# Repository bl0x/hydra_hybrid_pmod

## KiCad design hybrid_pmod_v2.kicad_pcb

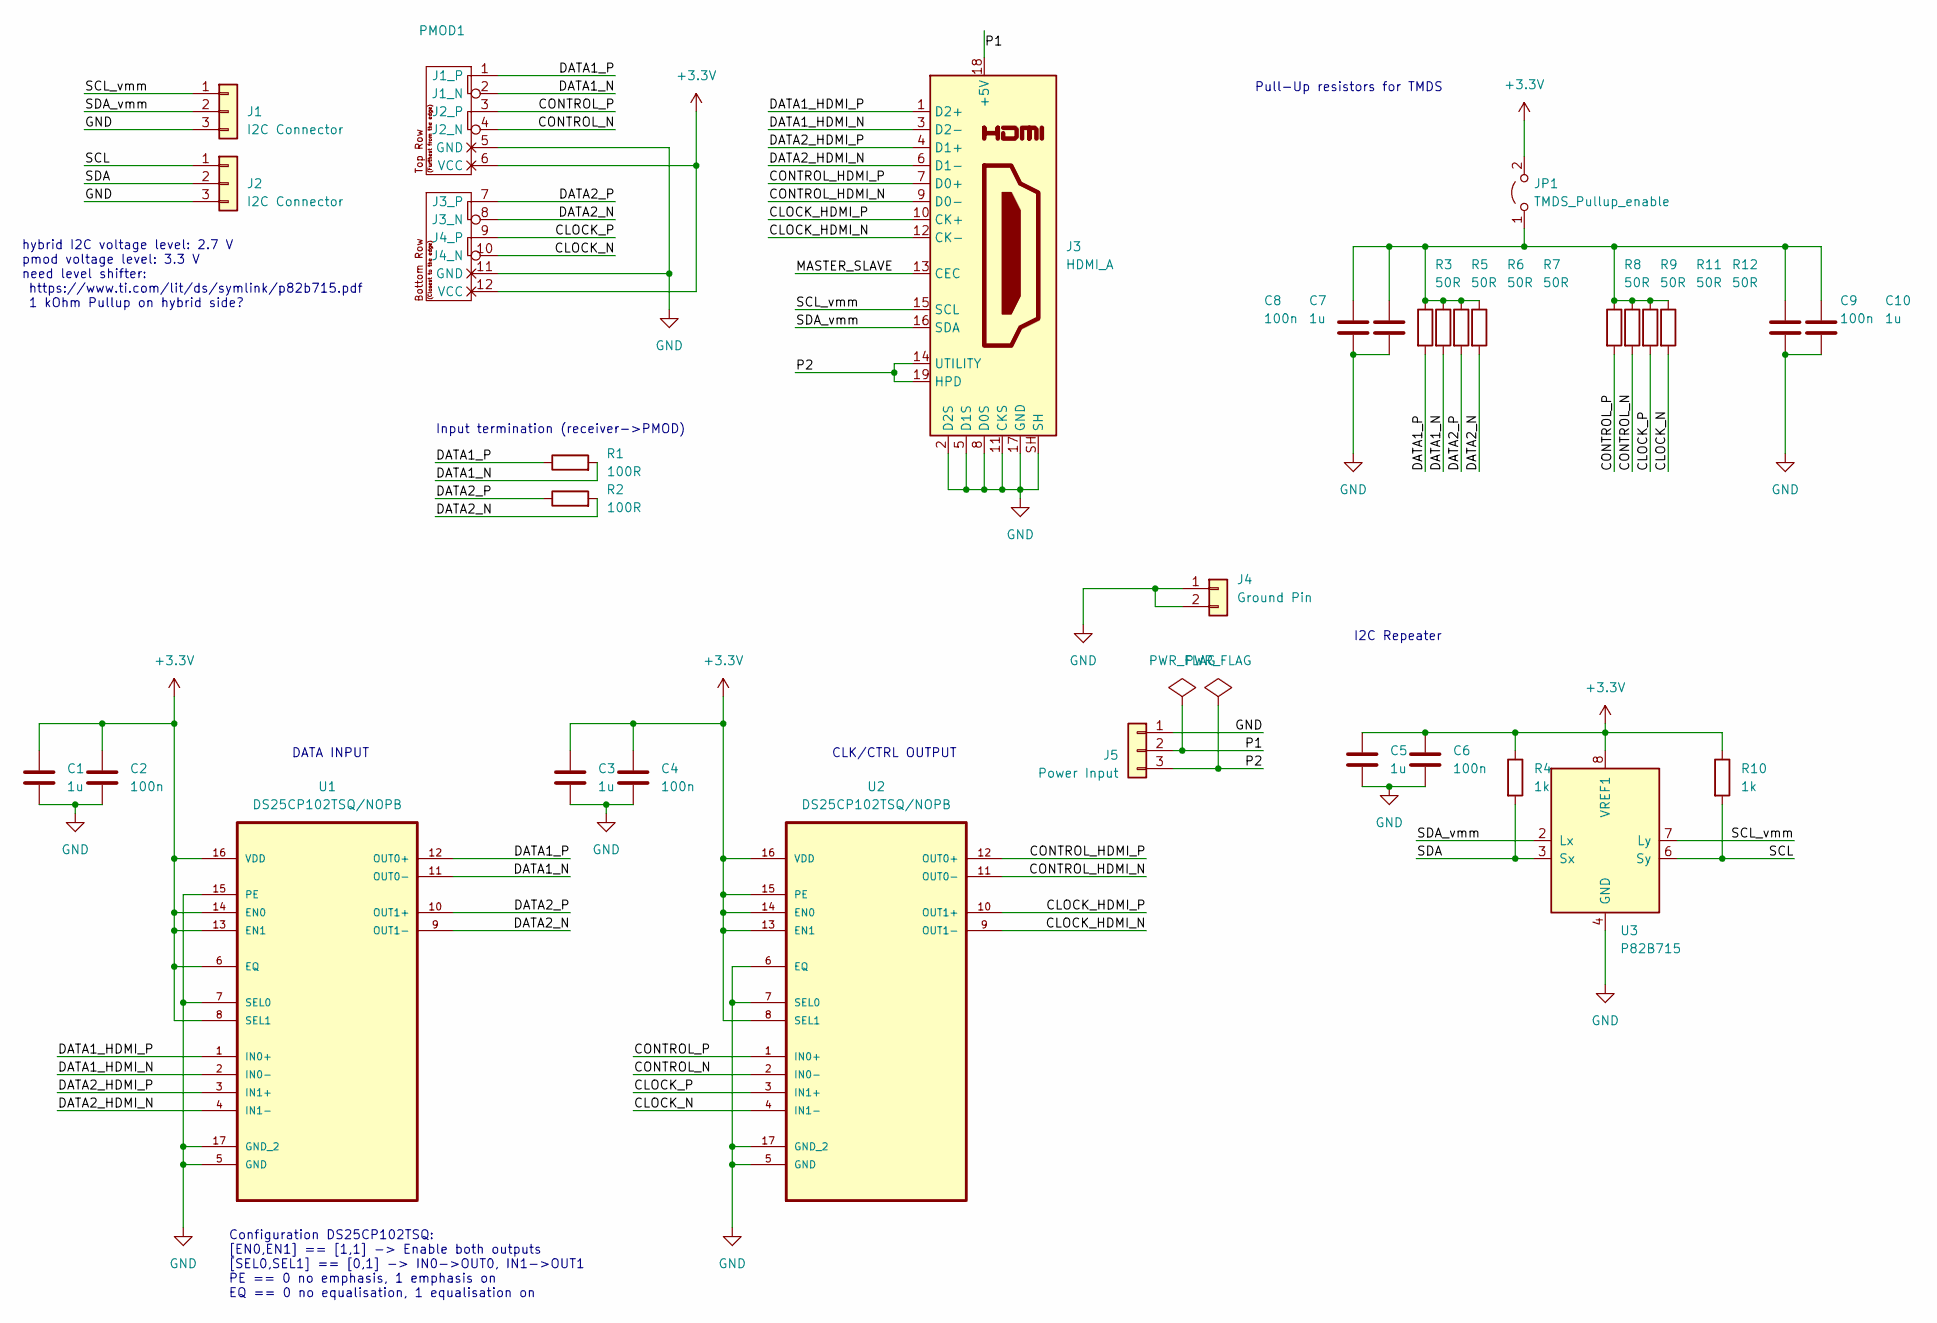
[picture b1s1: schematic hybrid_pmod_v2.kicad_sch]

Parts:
C1, C3, C5, C7, C10: 1u; C_0402_1005Metric_Pad0.74x0.62mm_HandSolder
C2, C4, C6, C8, C9: 100n; C_0402_1005Metric_Pad0.74x0.62mm_HandSolder
J1, J2: I2C Connector; PinHeader_1x03_P2.54mm_Vertical
J3: HDMI_A; HDMI_A_Molex_208658-1001_Horizontal
J4: Ground Pin; PinHeader_1x02_P2.54mm_Vertical
J5: Power Input; JST_XH_B3B-XH-A_1x03_P2.50mm_Vertical
JP1: TMDS_Pullup_enable; PinHeader_1x02_P2.54mm_Vertical
PMOD1: PMOD-Device-x2-Type-XHS; pmod_pin_array_6x2
R1, R2: 100R; R_0402_1005Metric_Pad0.72x0.64mm_HandSolder
R3, R5, R6, R7, R8, R9, R11, R12: 50R; R_0402_1005Metric_Pad0.72x0.64mm_HandSolder
R4, R10: 1k; R_0402_1005Metric_Pad0.72x0.64mm_HandSolder
U1, U2: DS25CP102TSQ/NOPB; QFN50P400X400X80-17N; MPN DS25CP102TSQ/NOPB
U3: P82B715; SOIC-8_3.9x4.9mm_P1.27mm

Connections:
+3.3V: C1.1, C2.1, C3.1, C4.1, C5.1, C6.1, JP1.2 (B), PMOD1.6 (VCC), PMOD1.12 (VCC), R4.1, R10.1, U1.6 (EQ), U1.8 (SEL1), U1.13 (EN1), U1.14 (EN0), U1.16 (VDD), U2.8 (SEL1), U2.13 (EN1), U2.14 (EN0), U2.15 (PE), U2.16 (VDD), U3.8 (VREF1)
/CLOCK_HDMI_N: J3.12 (CK-), U2.9 (OUT1-)
/CLOCK_HDMI_P: J3.10 (CK+), U2.10 (OUT1+)
/CLOCK_N: PMOD1.10 (J4_N), R12.2, U2.4 (IN1-)
/CLOCK_P: PMOD1.9 (J4_P), R11.2, U2.3 (IN1+)
/CONTROL_HDMI_N: J3.9 (D0-), U2.11 (OUT0-)
/CONTROL_HDMI_P: J3.7 (D0+), U2.12 (OUT0+)
/CONTROL_N: PMOD1.4 (J2_N), R9.2, U2.2 (IN0-)
/CONTROL_P: PMOD1.3 (J2_P), R8.2, U2.1 (IN0+)
/DATA1_HDMI_N: J3.3 (D2-), U1.2 (IN0-)
/DATA1_HDMI_P: J3.1 (D2+), U1.1 (IN0+)
/DATA1_N: PMOD1.2 (J1_N), R1.2, R5.2, U1.11 (OUT0-)
/DATA1_P: PMOD1.1 (J1_P), R1.1, R3.2, U1.12 (OUT0+)
/DATA2_HDMI_N: J3.6 (D1-), U1.4 (IN1-)
/DATA2_HDMI_P: J3.4 (D1+), U1.3 (IN1+)
/DATA2_N: PMOD1.8 (J3_N), R2.2, R7.2, U1.9 (OUT1-)
/DATA2_P: PMOD1.7 (J3_P), R2.1, R6.2, U1.10 (OUT1+)
/MASTER_SLAVE: J3.13 (CEC)
/P1: J3.18 (+5V), J5.2
/P2: J3.14 (UTILITY), J3.19 (HPD), J5.3
/SCL: J2.1, R10.2, U3.6 (Sy)
/SCL_vmm: J1.1, J3.15 (SCL), U3.7 (Ly)
/SDA: J2.2, R4.2, U3.3 (Sx)
/SDA_vmm: J1.2, J3.16 (SDA), U3.2 (Lx)
GND: C1.2, C2.2, C3.2, C4.2, C5.2, C6.2, C7.2, C8.2, C9.2, C10.2, J1.3, J2.3, J3.2 (D2S), J3.5 (D1S), J3.8 (D0S), J3.11 (CKS), J3.17 (GND), J3.SH, J4.1, J4.2, J5.1, PMOD1.5 (GND), PMOD1.11 (GND), U1.5 (GND), U1.7 (SEL0), U1.15 (PE), U1.17 (GND_2), U2.5 (GND), U2.6 (EQ), U2.7 (SEL0), U2.17 (GND_2), U3.4 (GND)
unnamed: C7.1, C8.1, C9.1, C10.1, JP1.1 (A), R3.1, R5.1, R6.1, R7.1, R8.1, R9.1, R11.1, R12.1

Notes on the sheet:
hybrid I2C voltage level: 2.7 V pmod voltage level: 3.3 V need level shifter: https://www.ti.com/lit/ds/symlink/p82b715.pdf 1 kOhm Pullup on hybrid side?
Configuration DS25CP102TSQ: [EN0,EN1] == [1,1] -> Enable both outputs [SEL0,SEL1] == [0,1] -> IN0->OUT0, IN1->OUT1 PE == 0 no emphasis, 1 emphasis on EQ == 0 no equalisation, 1 equalisation on
Input termination (receiver->PMOD)
CLK/CTRL OUTPUT
DATA INPUT
I2C Repeater
Pull-Up resistors for TMDS

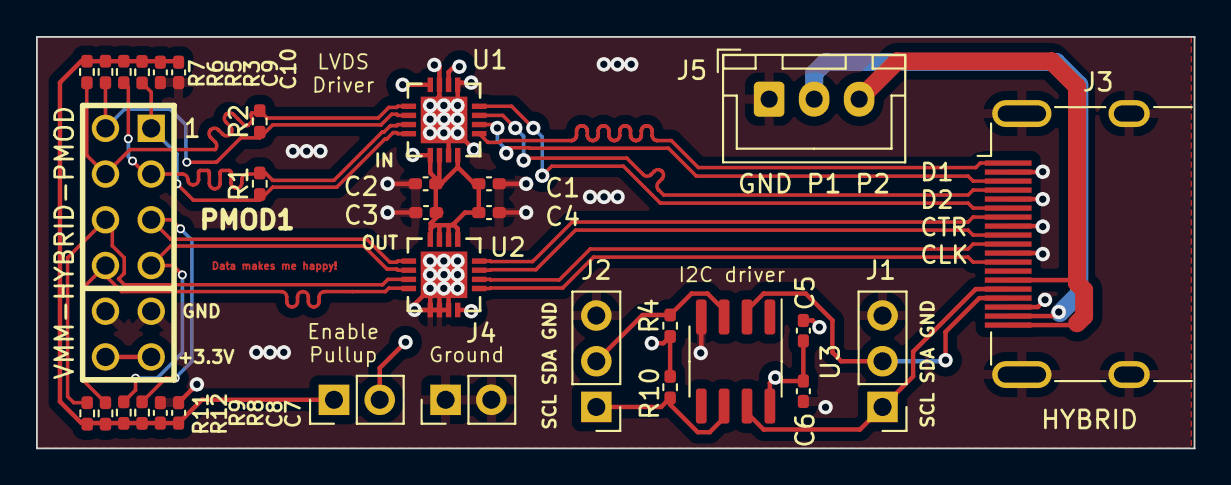
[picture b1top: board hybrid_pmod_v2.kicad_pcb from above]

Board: 4 copper layers, 64.3 x 22.9 mm, 32 parts (0 on the bottom side), 25 nets.

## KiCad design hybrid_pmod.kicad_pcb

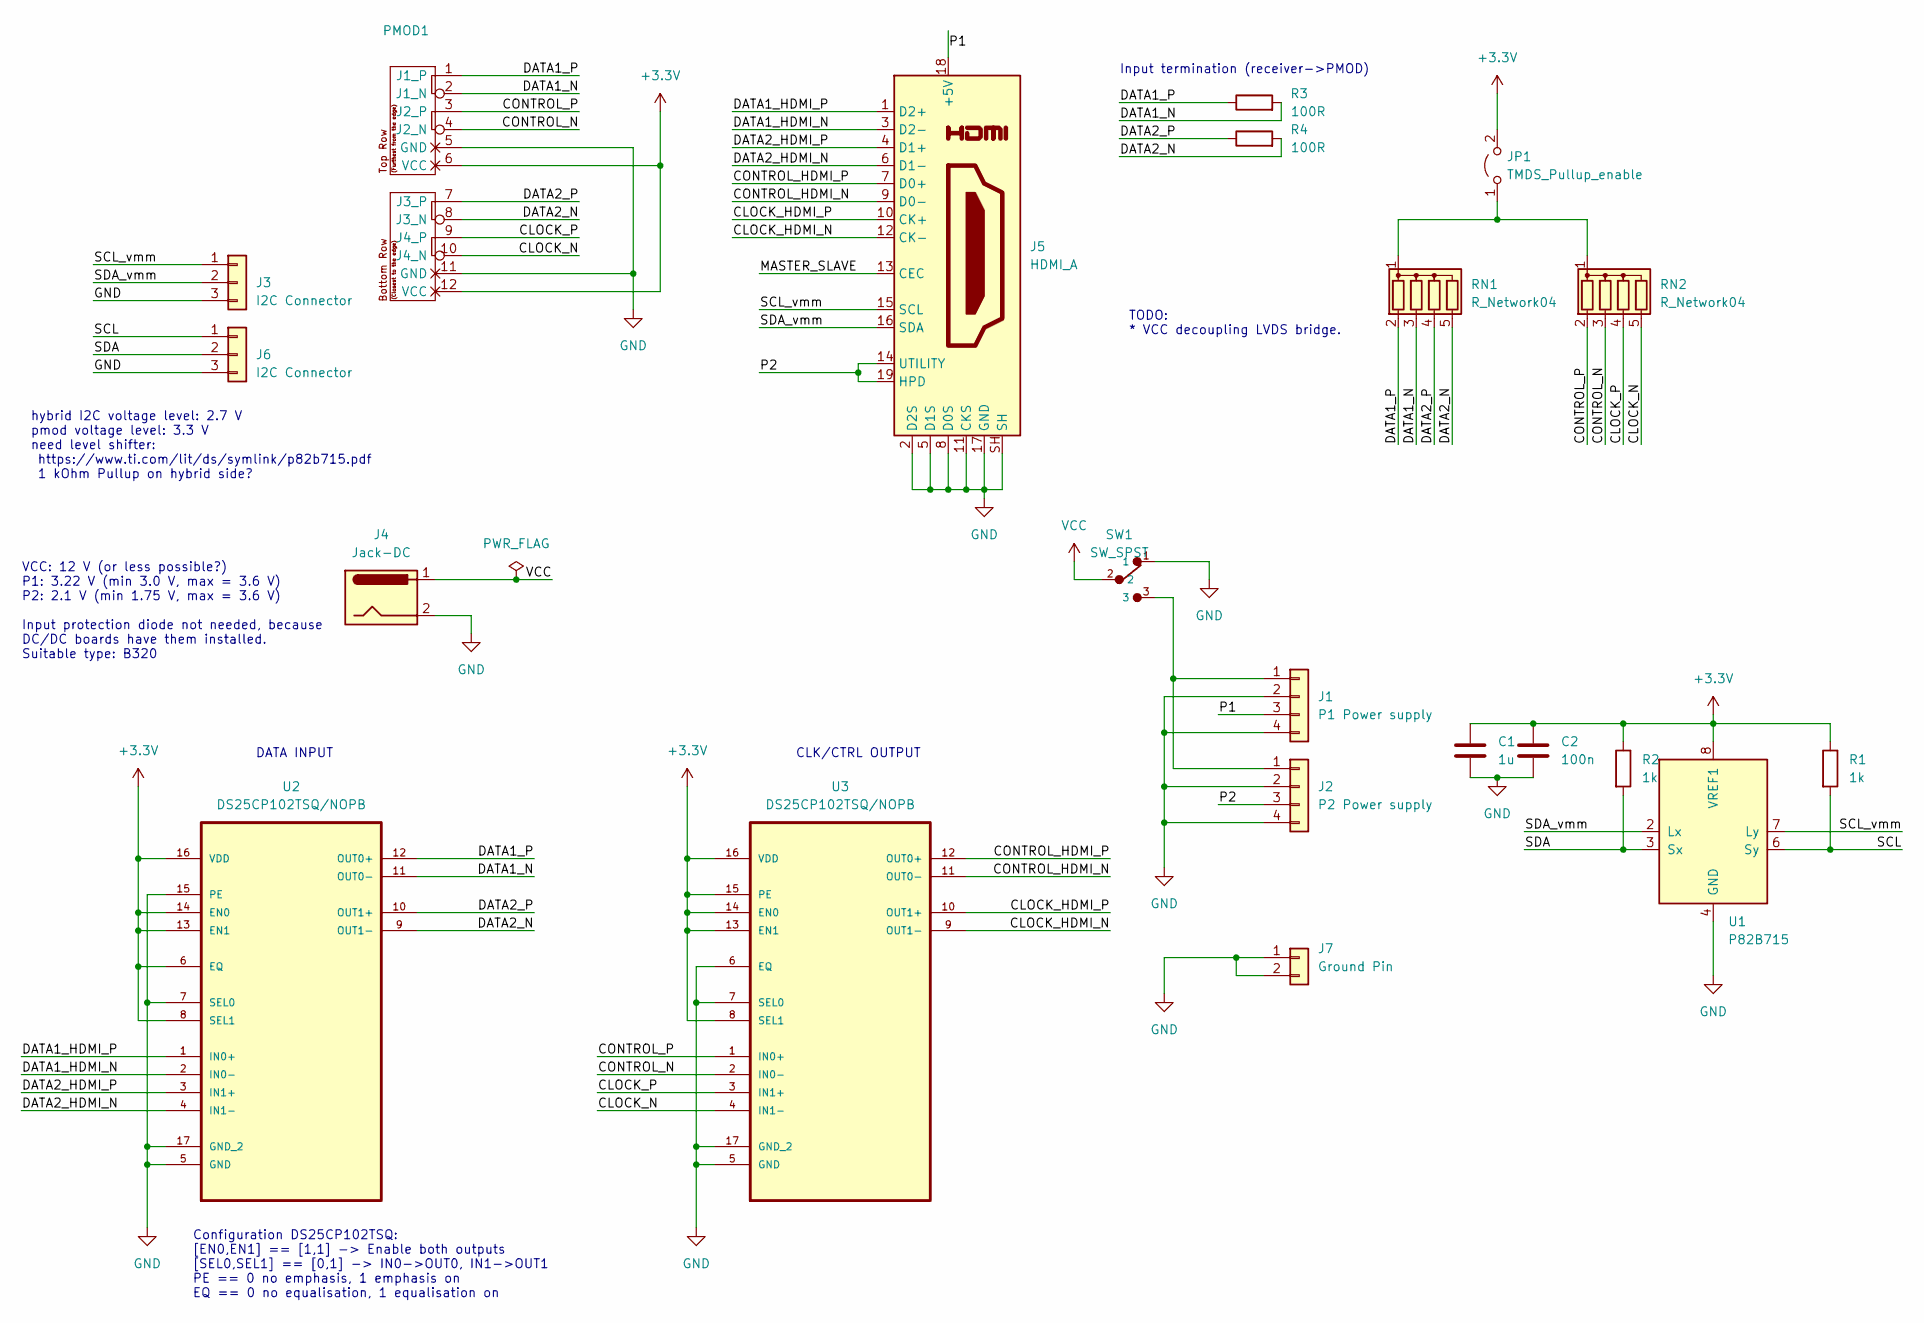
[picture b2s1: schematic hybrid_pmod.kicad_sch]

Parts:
C1: 1u; C_0603_1608Metric_Pad1.08x0.95mm_HandSolder
C2: 100n; C_0603_1608Metric_Pad1.08x0.95mm_HandSolder
J1: P1 Power supply; DC_DC_LM2596_small_short
J2: P2 Power supply; DC_DC_LM2596_small_short
J3, J6: I2C Connector; PinHeader_1x03_P2.54mm_Vertical
J4: Jack-DC; BarrelJack_Horizontal
J5: HDMI_A; HDMI_A_Molex_208658-1001_Horizontal
J7: Ground Pin; PinHeader_1x02_P2.54mm_Vertical
JP1: TMDS_Pullup_enable; PinHeader_1x02_P2.54mm_Vertical
PMOD1: PMOD-Device-x2-Type-XHS; pmod_pin_array_6x2
R1, R2: 1k; R_0603_1608Metric_Pad0.98x0.95mm_HandSolder
R3, R4: 100R
RN1, RN2: R_Network04; R_Cat16-4
SW1: SW_SPST; SW_1101M2S3CQE2
U1: P82B715; SOIC-8_3.9x4.9mm_P1.27mm
U2, U3: DS25CP102TSQ/NOPB; QFN50P400X400X80-17N; MPN DS25CP102TSQ/NOPB

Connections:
+3.3V: C1.1, C2.1, JP1.2 (B), PMOD1.6 (VCC), PMOD1.12 (VCC), R1.1, R2.1, U1.8 (VREF1), U2.6 (EQ), U2.8 (SEL1), U2.13 (EN1), U2.14 (EN0), U2.16 (VDD), U3.8 (SEL1), U3.13 (EN1), U3.14 (EN0), U3.15 (PE), U3.16 (VDD)
/CLOCK_HDMI_N: J5.12 (CK-), U3.9 (OUT1-)
/CLOCK_HDMI_P: J5.10 (CK+), U3.10 (OUT1+)
/CLOCK_N: PMOD1.10 (J4_N), RN2.5 (R4), U3.4 (IN1-)
/CLOCK_P: PMOD1.9 (J4_P), RN2.4 (R3), U3.3 (IN1+)
/CONTROL_HDMI_N: J5.9 (D0-), U3.11 (OUT0-)
/CONTROL_HDMI_P: J5.7 (D0+), U3.12 (OUT0+)
/CONTROL_N: PMOD1.4 (J2_N), RN2.3 (R2), U3.2 (IN0-)
/CONTROL_P: PMOD1.3 (J2_P), RN2.2 (R1), U3.1 (IN0+)
/DATA1_HDMI_N: J5.3 (D2-), U2.2 (IN0-)
/DATA1_HDMI_P: J5.1 (D2+), U2.1 (IN0+)
/DATA1_N: PMOD1.2 (J1_N), R3.2, RN1.3 (R2), U2.11 (OUT0-)
/DATA1_P: PMOD1.1 (J1_P), R3.1, RN1.2 (R1), U2.12 (OUT0+)
/DATA2_HDMI_N: J5.6 (D1-), U2.4 (IN1-)
/DATA2_HDMI_P: J5.4 (D1+), U2.3 (IN1+)
/DATA2_N: PMOD1.8 (J3_N), R4.2, RN1.5 (R4), U2.9 (OUT1-)
/DATA2_P: PMOD1.7 (J3_P), R4.1, RN1.4 (R3), U2.10 (OUT1+)
/MASTER_SLAVE: J5.13 (CEC)
/P1: J1.3, J5.18 (+5V)
/P2: J2.3, J5.14 (UTILITY), J5.19 (HPD)
/SCL: J6.1, R1.2, U1.6 (Sy)
/SCL_vmm: J3.1, J5.15 (SCL), U1.7 (Ly)
/SDA: J6.2, R2.2, U1.3 (Sx)
/SDA_vmm: J3.2, J5.16 (SDA), U1.2 (Lx)
GND: C1.2, C2.2, J1.2, J1.4, J2.2, J2.4, J3.3, J4.2, J5.2 (D2S), J5.5 (D1S), J5.8 (D0S), J5.11 (CKS), J5.17 (GND), J5.SH, J6.3, J7.1, J7.2, PMOD1.5 (GND), PMOD1.11 (GND), SW1.1, U1.4 (GND), U2.5 (GND), U2.7 (SEL0), U2.15 (PE), U2.17 (GND_2), U3.5 (GND), U3.6 (EQ), U3.7 (SEL0), U3.17 (GND_2)
unnamed: J1.1, J2.1, SW1.3
unnamed: JP1.1 (A), RN1.1 (common), RN2.1 (common)
VCC: J4.1, SW1.2

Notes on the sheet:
hybrid I2C voltage level: 2.7 V pmod voltage level: 3.3 V need level shifter: https://www.ti.com/lit/ds/symlink/p82b715.pdf 1 kOhm Pullup on hybrid side?
VCC: 12 V (or less possible?) P1: 3.22 V (min 3.0 V, max = 3.6 V) P2: 2.1 V (min 1.75 V, max = 3.6 V) Input protection diode not needed, because DC/DC boards have them installed. Suitable type: B320
Configuration DS25CP102TSQ: [EN0,EN1] == [1,1] -> Enable both outputs [SEL0,SEL1] == [0,1] -> IN0->OUT0, IN1->OUT1 PE == 0 no emphasis, 1 emphasis on EQ == 0 no equalisation, 1 equalisation on
Input termination (receiver->PMOD)
CLK/CTRL OUTPUT
DATA INPUT
TODO: * VCC decoupling LVDS bridge.

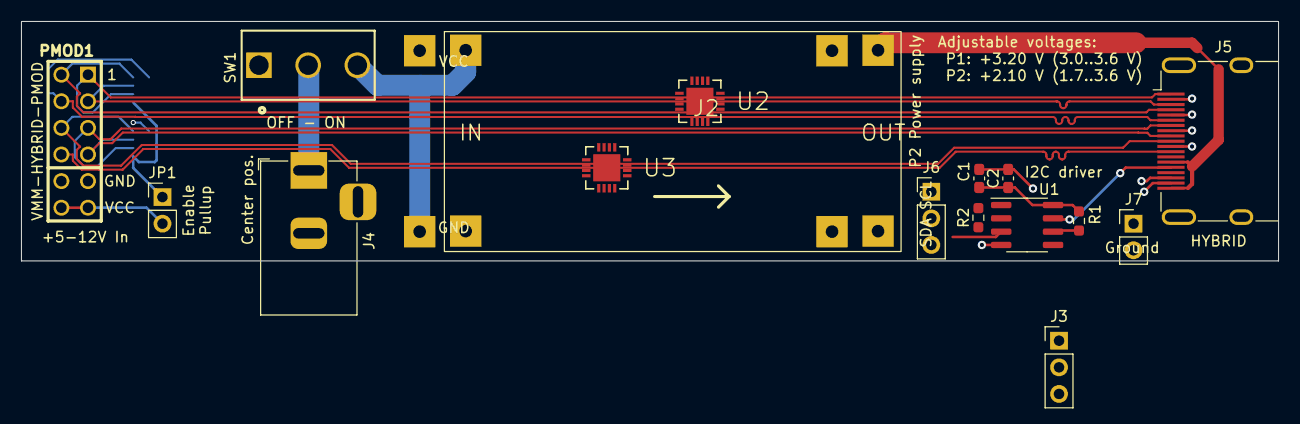
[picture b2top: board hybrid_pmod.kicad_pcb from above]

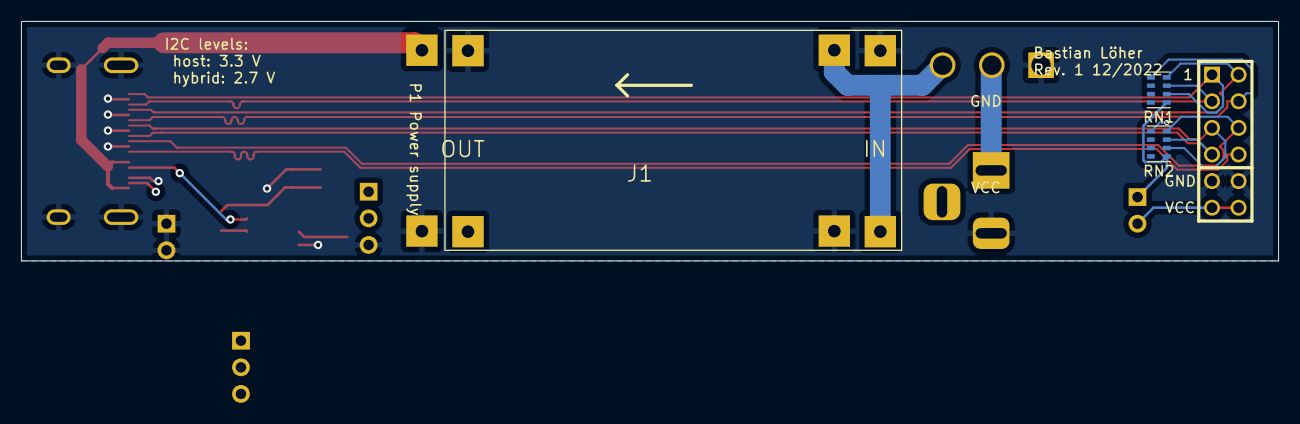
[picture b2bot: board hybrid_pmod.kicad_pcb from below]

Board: 4 copper layers, 120.0 x 22.9 mm, 19 parts (3 on the bottom side), 27 nets.

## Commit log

2023-04-24 Initial commit.
2023-05-11 New version, now with external power supply.
2023-05-11 Allow images and pdf schematics in git.
2023-07-13 Many changes, suggestions from H. T. Johansson.
